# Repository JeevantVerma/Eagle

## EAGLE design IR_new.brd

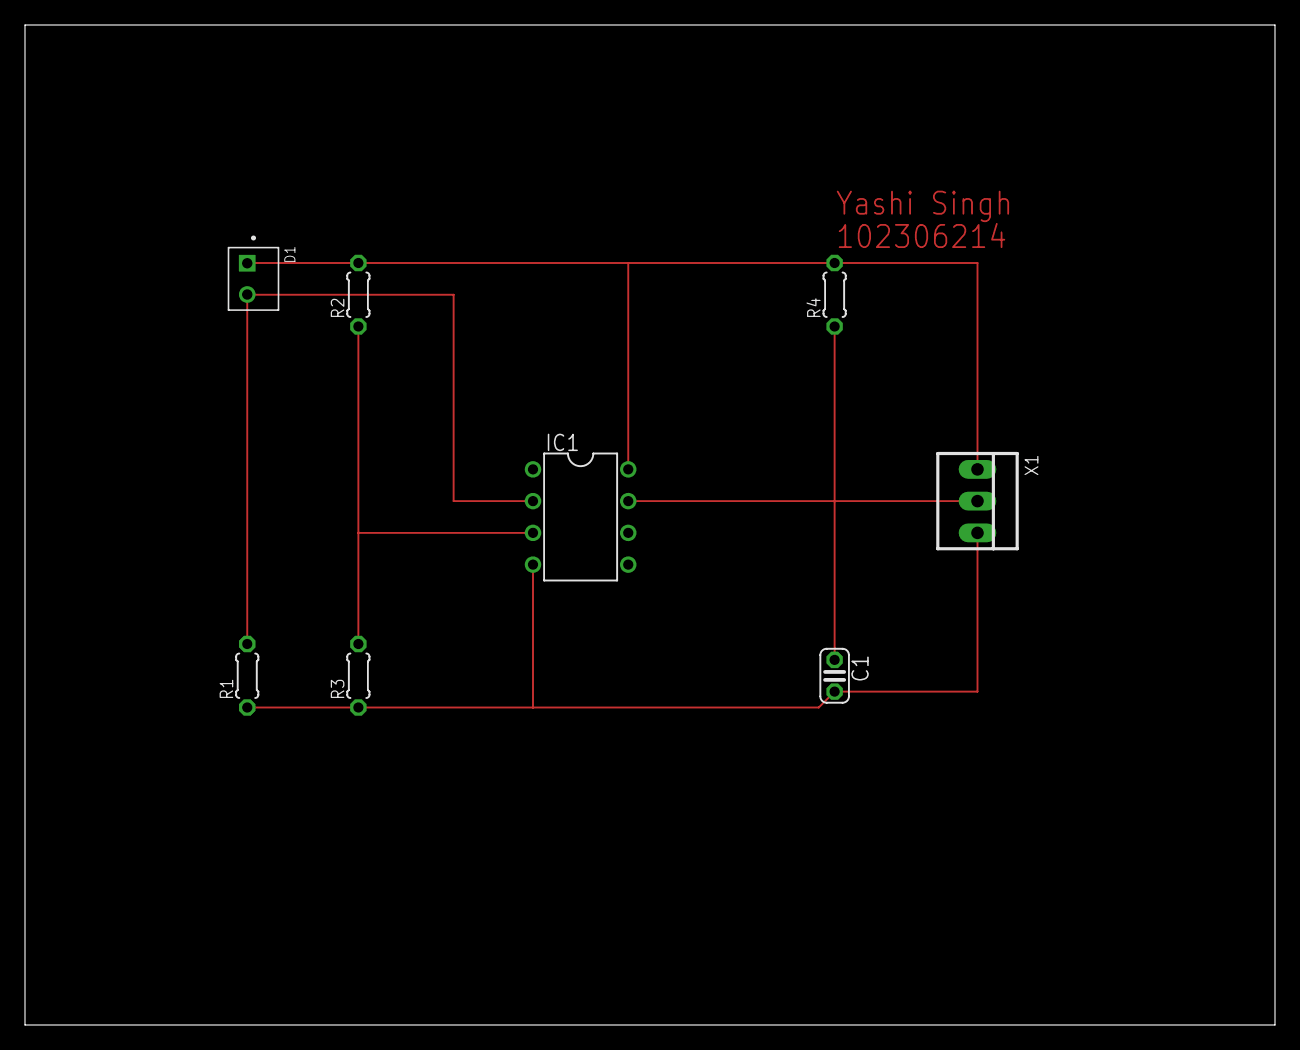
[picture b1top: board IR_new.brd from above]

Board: 2 copper layers, 100.0 x 80.0 mm, 8 parts (0 on the bottom side), 6 nets.

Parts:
C1: 10pf; C025-024X044
D1: BPW41N; DIO_BPW41N
IC1: LM311N; DIL08
R1: 120k; 0204/5
R2: 100k; 0204/5
R3: 22k; 0204/5
R4: 1k; 0204/5
X1: 22-23-2031

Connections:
unnamed: IC1.7, X1.2
unnamed: D1.A, IC1.2, R1.2
unnamed: C1.2, IC1.1, IC1.4, R1.1, R3.1, X1.3
unnamed: D1.C, IC1.8, R2.2, R4.2, X1.1
unnamed: IC1.3, R2.1, R3.2
S$1: C1.1, R4.1

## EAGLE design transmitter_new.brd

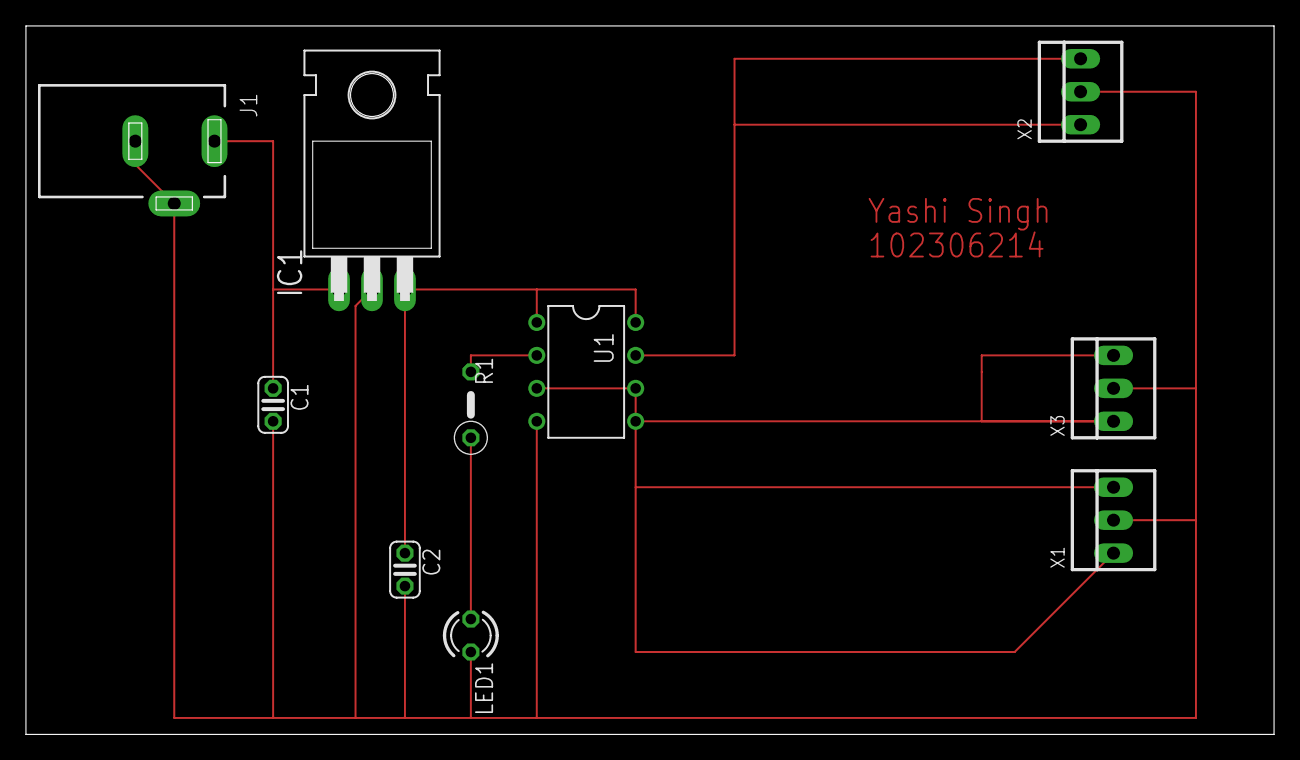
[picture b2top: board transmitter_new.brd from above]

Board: 2 copper layers, 96.2 x 54.6 mm, 10 parts (0 on the bottom side), 8 nets.

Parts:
C1: 10uF; C025-024X044
C2: 10PF; C025-024X044
IC1: 7805T; TO220H
J1: DCJ0202
LED1: LED3MM
R1: 330ohm; 0207/5V
U1: ATTINY85-20P; PDIP08_300MIL
X1, X2, X3: 22-23-2031

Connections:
unnamed: C2.1, IC1.3, U1.1, U1.8
unnamed: U1.3, X1.1, X1.3
unnamed: C1.2, C2.2, IC1.2, J1.2, J1.3, LED1.K, U1.4, X1.2, X2.2, X3.2
unnamed: R1.2, U1.2
unnamed: U1.7, X2.1, X2.3
unnamed: U1.5, X3.1, X3.3
unnamed: LED1.A, R1.1
unnamed: C1.1, IC1.1, J1.1

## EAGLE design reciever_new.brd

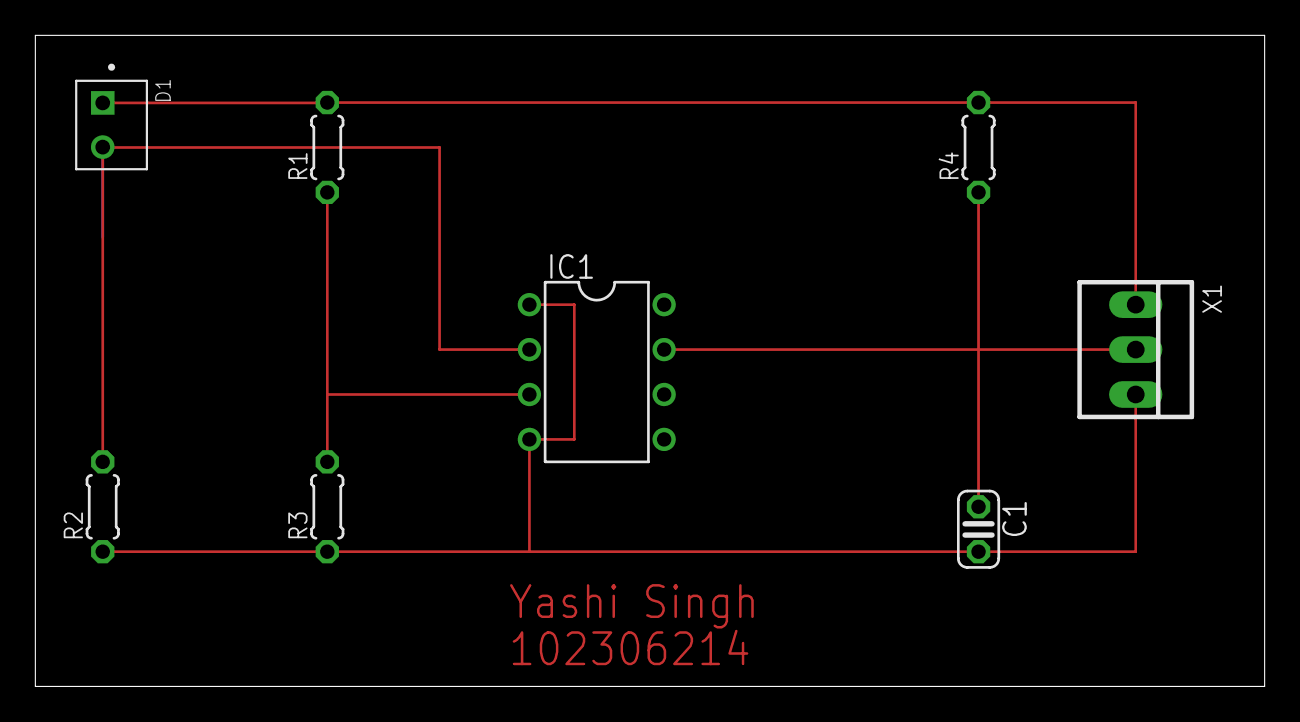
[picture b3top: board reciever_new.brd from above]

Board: 2 copper layers, 69.5 x 36.8 mm, 8 parts (0 on the bottom side), 5 nets.

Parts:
C1: C025-024X044
D1: BPW41N; DIO_BPW41N
IC1: LM311N; DIL08
R1: 100k; 0204/5
R2: 120K; 0204/5
R3: 22k; 0204/5
R4: 1k; 0204/5
X1: 22-23-2031

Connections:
unnamed: D1.A, IC1.2, R2.2
unnamed: C1.1, IC1.7, R4.1, X1.2
unnamed: D1.C, R1.2, R4.2, X1.1
unnamed: IC1.3, R1.1, R3.2
unnamed: C1.2, IC1.1, IC1.4, R2.1, R3.1, X1.3

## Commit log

2025-04-29 added files
